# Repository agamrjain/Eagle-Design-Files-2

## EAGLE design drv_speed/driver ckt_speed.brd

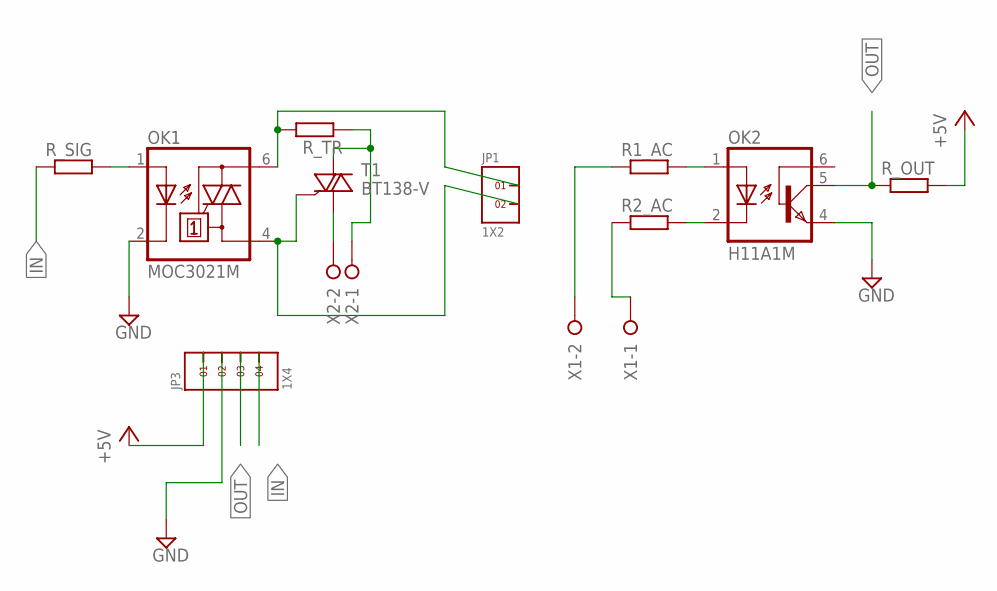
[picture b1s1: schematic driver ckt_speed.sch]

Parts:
JP1: 1X2
JP3: 1X4
OK1: MOC3021M; DIL06
OK2: H11A1M; DIL06
R1_AC, R2_AC: R-EU_0411/15; 0411/15
R_OUT: RR1206; R1206
R_SIG: RR1206; R1206
R_TR: RR1206; R1206
T1: BT138-V; TO220BV
X1, X2: W237-02P; W237-132

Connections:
+5V: JP3.1, R_OUT.2
AC1: R1_AC.1, X1.2
GND: JP3.2, OK1.2 (C), OK2.4 (EMI)
IN: JP3.4, R_SIG.1
unnamed: JP1.1, OK1.6 (A2), R_TR.2
unnamed: R_TR.1, T1.T2 (A2), X2.1
unnamed: T1.T1 (A1), X2.2
unnamed: OK1.1 (A), R_SIG.2
unnamed: OK2.1 (A), R1_AC.2
unnamed: OK2.2 (C), R2_AC.2
unnamed: JP1.2, OK1.4 (A1), T1.G
unnamed: R2_AC.1, X1.1
OUT: JP3.3, OK2.5 (COL), R_OUT.1

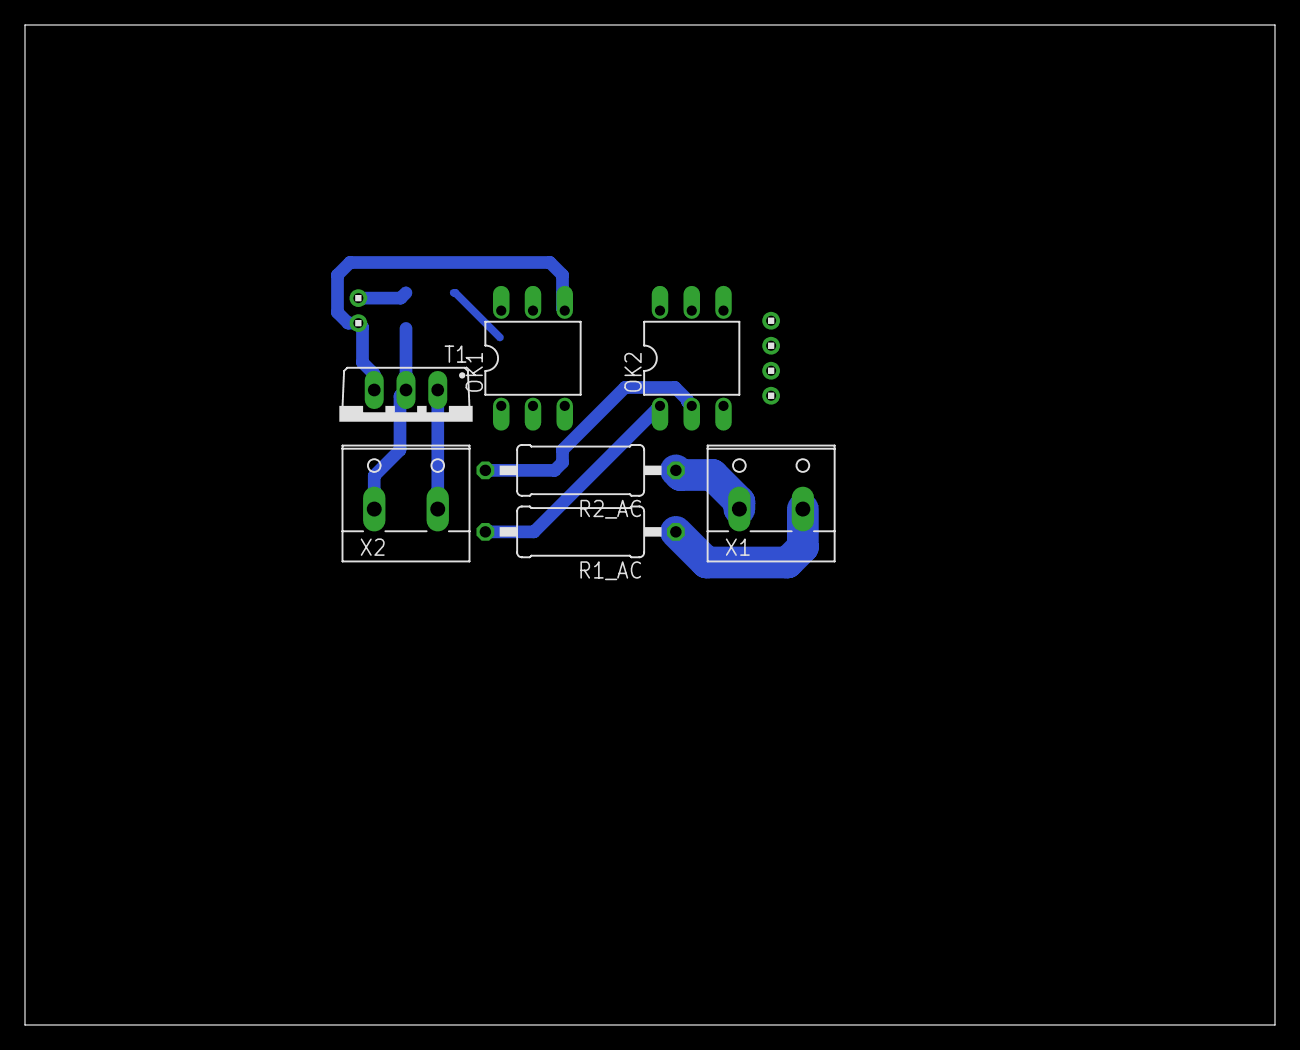
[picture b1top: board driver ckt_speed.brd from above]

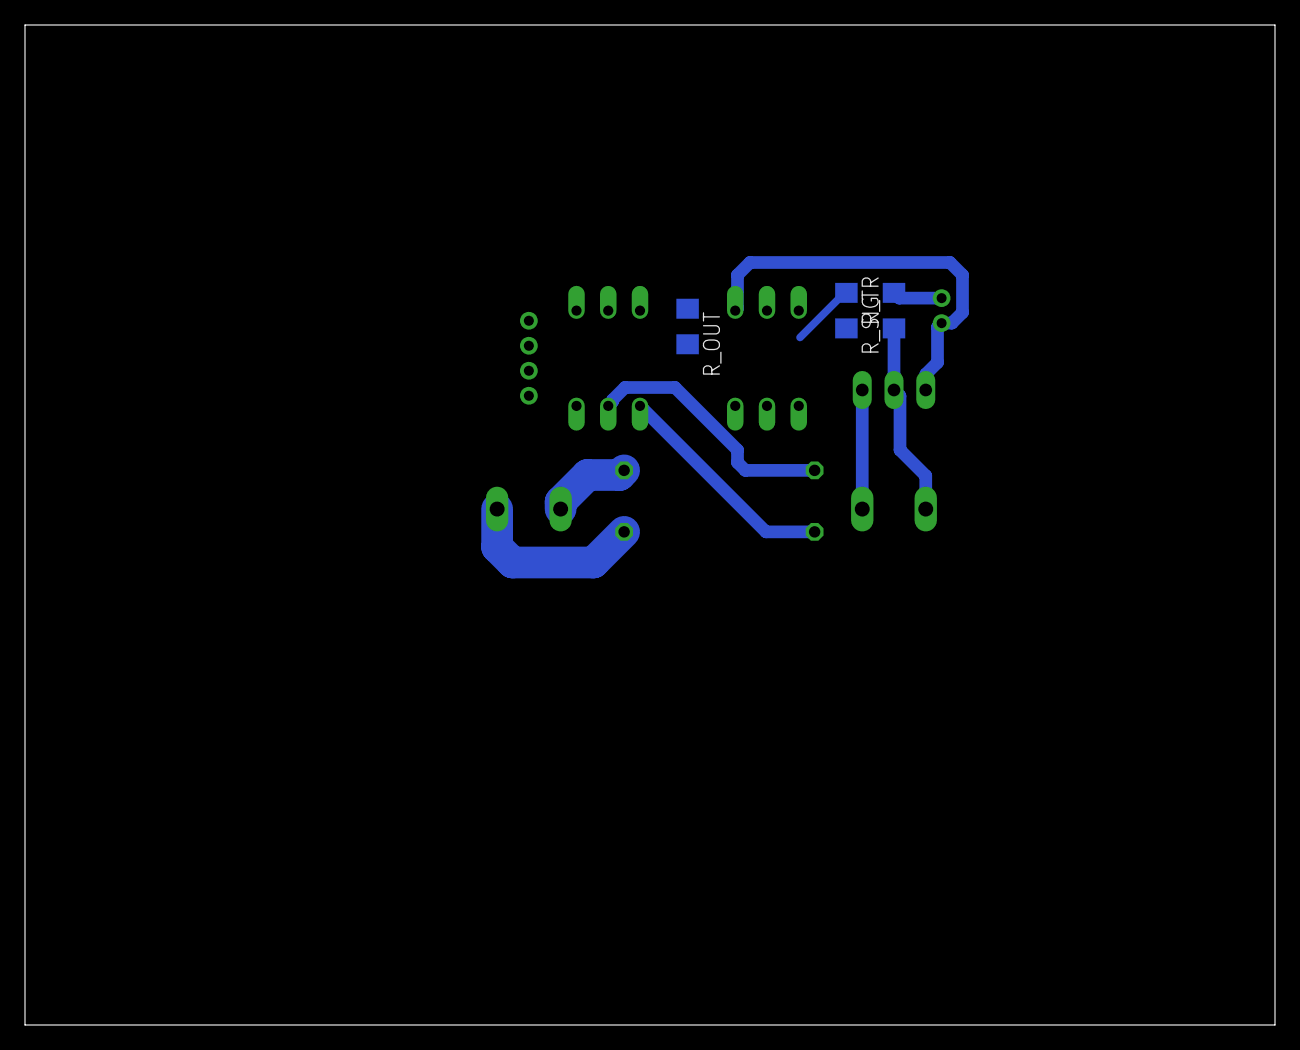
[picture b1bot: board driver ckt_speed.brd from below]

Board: 2 copper layers, 100.0 x 80.0 mm, 12 parts (3 on the bottom side), 13 nets.

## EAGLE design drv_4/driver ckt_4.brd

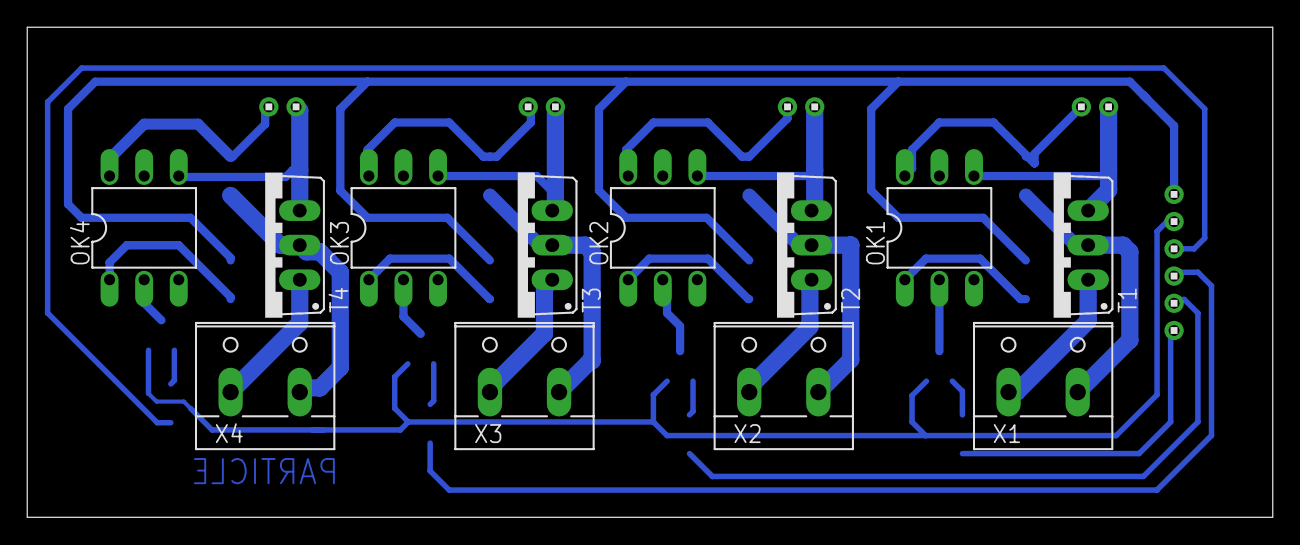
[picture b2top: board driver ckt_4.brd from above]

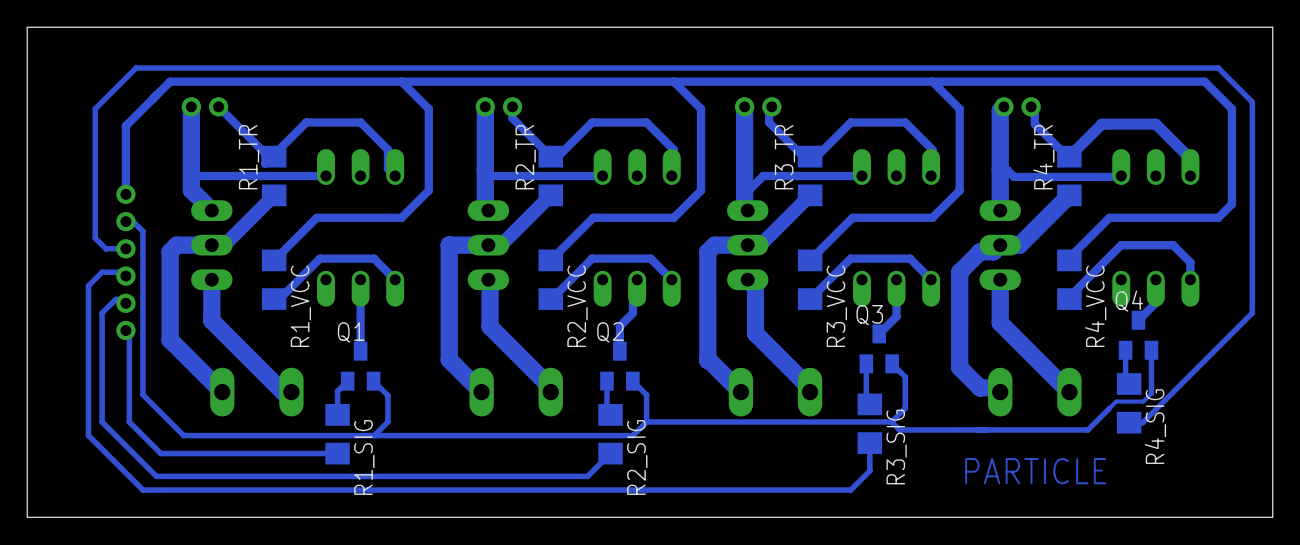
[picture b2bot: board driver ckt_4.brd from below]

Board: 2 copper layers, 91.5 x 36.0 mm, 33 parts (16 on the bottom side), 34 nets.

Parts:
JP1, JP2, JP3, JP4: 1X2
OK1, OK2, OK3, OK4: MOC3021M; DIL06
Q1, Q2, Q3, Q4: BC848SMD; SOT23
R1_SIG, R1_TR, R1_VCC, R2_SIG, R2_TR, R2_VCC, R3_SIG, R3_TR, R3_VCC, R4_SIG, R4_TR, R4_VCC: R1206
T1, T2, T3, T4: BT138-V; TO220BV
U$1: 1X6
X1, X2, X3, X4: W237-132

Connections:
+5V: R1_VCC.1, R2_VCC.1, R3_VCC.1, R4_VCC.1, U$1.1
IN1: R1_SIG.2, U$1.6
IN2: R2_SIG.2, U$1.5
IN3: R3_SIG.2, U$1.4
IN4: R4_SIG.2, U$1.3
unnamed: JP1.1, OK1.6, R1_TR.2
unnamed: R1_TR.1, T1.T2, X1.2
unnamed: T1.T1, X1.1
unnamed: OK1.1, R1_VCC.2
unnamed: OK1.2, Q1.3
unnamed: JP2.2, OK2.4, T2.G
unnamed: JP1.2, OK1.4, T1.G
unnamed: JP2.1, OK2.6, R2_TR.2
unnamed: Q1.1, R1_SIG.1
unnamed: R2_TR.1, T2.T2, X2.2
unnamed: Q2.1, R2_SIG.1
unnamed: T2.T1, X2.1
unnamed: OK2.1, R2_VCC.2
unnamed: OK2.2, Q2.3
unnamed: JP3.2, OK3.4, T3.G
unnamed: JP3.1, OK3.6, R3_TR.2
unnamed: R3_TR.1, T3.T2, X3.2
unnamed: Q3.1, R3_SIG.1
unnamed: T3.T1, X3.1
unnamed: OK3.1, R3_VCC.2
unnamed: OK3.2, Q3.3
unnamed: JP4.2, OK4.4, T4.G
unnamed: JP4.1, OK4.6, R4_TR.2
unnamed: R4_TR.1, T4.T2, X4.2
unnamed: Q4.1, R4_SIG.1
unnamed: T4.T1, X4.1
unnamed: OK4.1, R4_VCC.2
unnamed: OK4.2, Q4.3
PE: Q1.2, Q2.2, Q3.2, Q4.2, U$1.2

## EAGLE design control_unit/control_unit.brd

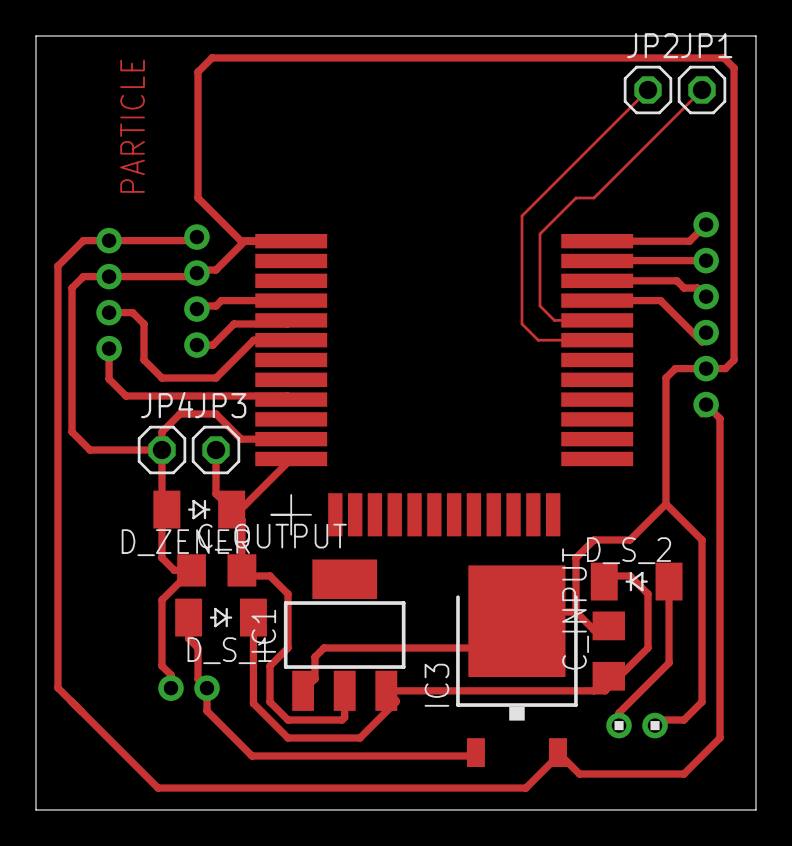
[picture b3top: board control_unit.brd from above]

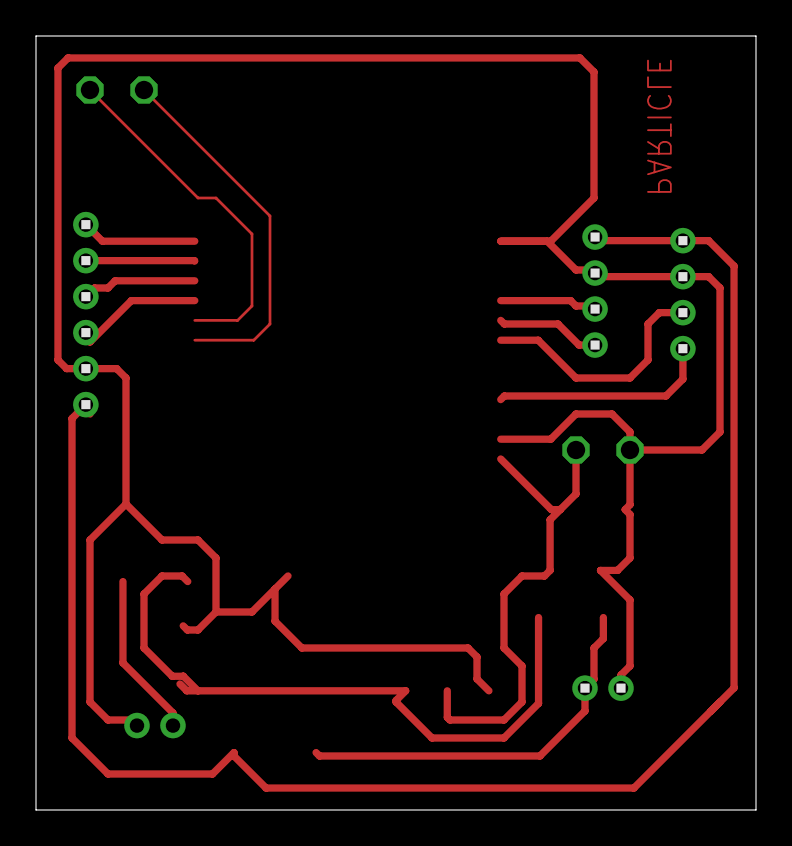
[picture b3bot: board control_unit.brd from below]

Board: 2 copper layers, 40.0 x 43.0 mm, 17 parts (4 on the bottom side), 16 nets.

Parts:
2_DEVICE_TERMINAL: 1X4
4_DEVICE_TERMINAL: 1X6
C_INPUT: C1206
C_OUTPUT: C1206
D_S_1, D_S_2: CGRM4001-G; SOD-123_MINI-SMA
D_ZENER: CGRM4001-G; SOD-123_MINI-SMA
IC1: LM1117MPX-5.0; SOT223
IC3: 7808DT; TO252
JP1, JP2, JP3, JP4: 1X01
SPEED_TERMINAL: 1X4
SUPPLY_1, SUPPLY_2: 1X2
U$1: HZX_MODULE; SMD_PAD_VERSION

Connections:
3.3V: C_OUTPUT.2, D_ZENER.C, IC1.2, JP3.1, U$1.P$12
5V: 2_DEVICE_TERMINAL.1, 4_DEVICE_TERMINAL.1, IC3.2, SPEED_TERMINAL.1
CLK: JP1.1, U$1.P$32
DIO: JP2.1, U$1.P$31
GND: 2_DEVICE_TERMINAL.2, 4_DEVICE_TERMINAL.2, C_INPUT.2, C_OUTPUT.1, D_ZENER.A, IC1.1, IC3.3, JP4.1, SPEED_TERMINAL.2, SUPPLY_1.2, SUPPLY_2.2, U$1.P$01, U$1.P$11
IN28: SPEED_TERMINAL.4, U$1.P$09
unnamed: D_S_1.A, IC3.1, SUPPLY_1.1
unnamed: C_INPUT.1, D_S_1.C, D_S_2.C, IC1.3
unnamed: D_S_2.A, SUPPLY_2.1
O17: 4_DEVICE_TERMINAL.3, U$1.P$33
O18: 4_DEVICE_TERMINAL.4, U$1.P$34
O19: 4_DEVICE_TERMINAL.5, U$1.P$35
O20: 4_DEVICE_TERMINAL.6, U$1.P$36
O23: 2_DEVICE_TERMINAL.3, U$1.P$04
O24: 2_DEVICE_TERMINAL.4, U$1.P$05
O25: SPEED_TERMINAL.3, U$1.P$06

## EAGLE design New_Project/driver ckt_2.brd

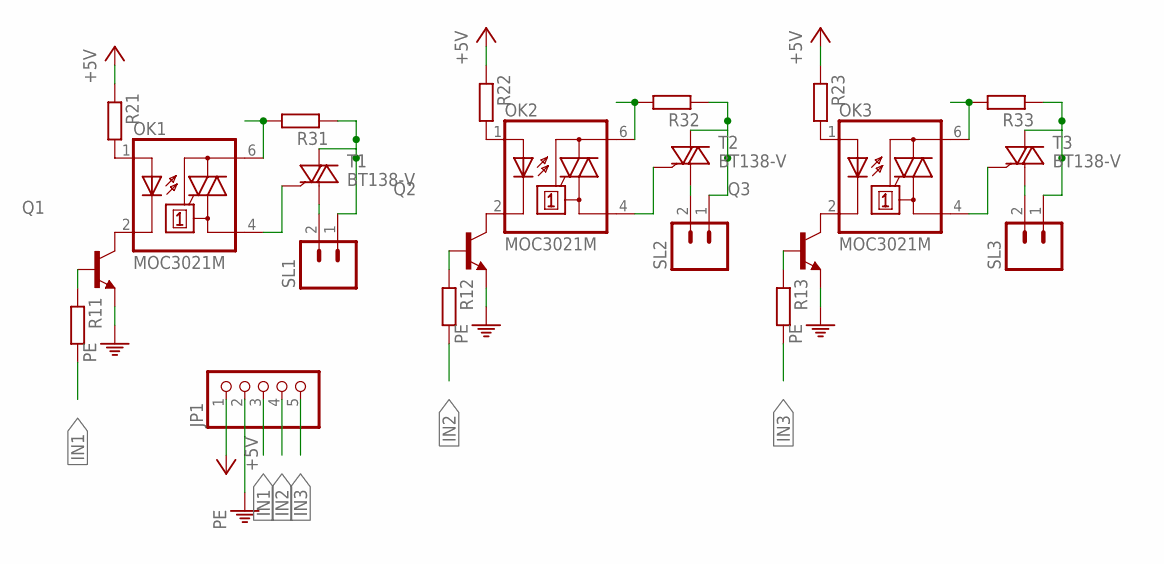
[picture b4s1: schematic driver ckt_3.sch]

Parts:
JP1: PINHD-1X5; 1X05
OK1, OK2, OK3: MOC3021M; DIL06
Q1, Q2, Q3: -NPN-SOT23-EBC; SOT23-EBC
R11, R12, R13, R21, R22, R23, R31, R32, R33: RR1206; R1206
SL1, SL2, SL3: M02; 02P
T1, T2, T3: BT138-V; TO220BV

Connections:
+5V: JP1.1, R21.1, R22.1, R23.1
IN1: JP1.3, R11.2
IN2: JP1.4, R12.2
IN3: JP1.5, R13.2
unnamed: OK1.6 (A2), R31.2
unnamed: R31.1, SL1.1, T1.T2 (A2)
unnamed: SL1.2, T1.T1 (A1)
unnamed: OK1.1 (A), R21.2
unnamed: OK1.2 (C), Q1.C
unnamed: OK2.4 (A1), T2.G
unnamed: OK1.4 (A1), T1.G
unnamed: OK2.6 (A2), R32.2
unnamed: Q1.B, R11.1
unnamed: R32.1, SL2.1, T2.T2 (A2)
unnamed: Q2.B, R12.1
unnamed: SL2.2, T2.T1 (A1)
unnamed: OK2.1 (A), R22.2
unnamed: OK2.2 (C), Q2.C
unnamed: OK3.4 (A1), T3.G
unnamed: OK3.6 (A2), R33.2
unnamed: R33.1, SL3.1, T3.T2 (A2)
unnamed: Q3.B, R13.1
unnamed: SL3.2, T3.T1 (A1)
unnamed: OK3.1 (A), R23.2
unnamed: OK3.2 (C), Q3.C
PE: JP1.2, Q1.E, Q2.E, Q3.E

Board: 2 copper layers, 22 parts (0 on the bottom side), 26 nets, no tracks yet.

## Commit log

2018-08-27 Created Readme file.
2018-08-27 upload#1
